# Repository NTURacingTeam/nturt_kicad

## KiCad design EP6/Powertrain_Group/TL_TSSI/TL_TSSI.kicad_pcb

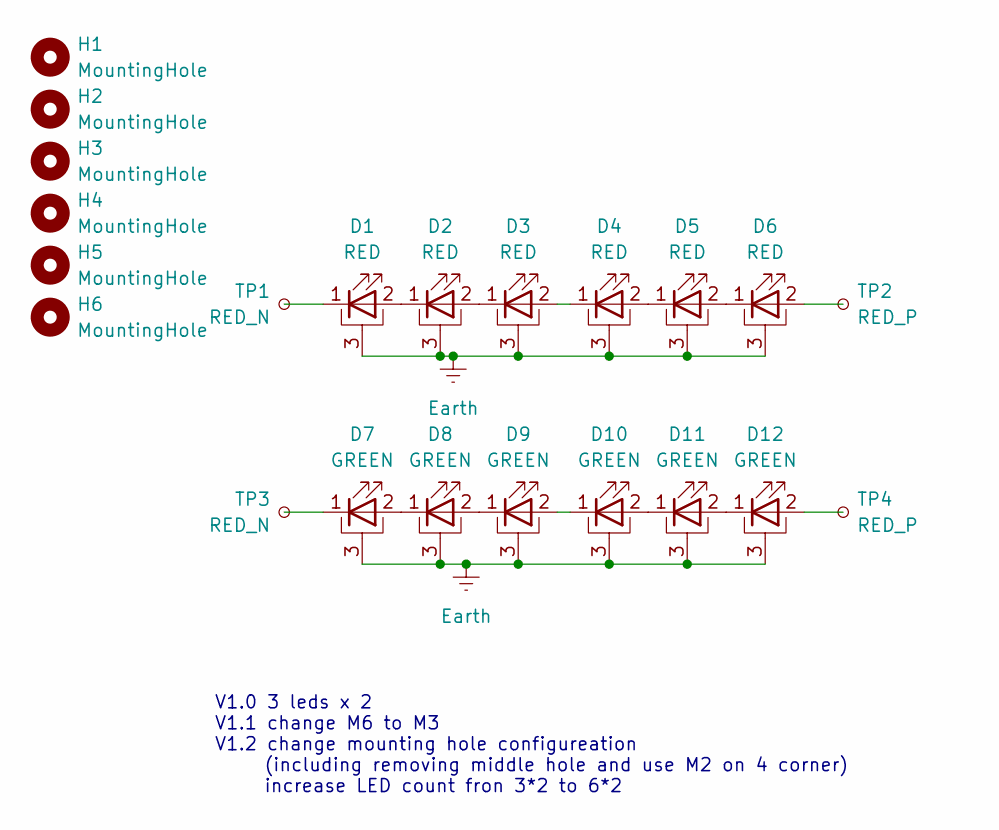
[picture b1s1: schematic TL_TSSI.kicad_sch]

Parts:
D1, D2, D3, D4, D5, D6: RED; LED_1W_3W_R8
D7, D8, D9, D10, D11, D12: GREEN; LED_1W_3W_R8
H1, H2, H3, H4, H5, H6: MountingHole; MountingHole_2.2mm_M2
TP1, TP3: RED_N; TestPoint_Pad_4.0x4.0mm
TP2, TP4: RED_P; TestPoint_Pad_4.0x4.0mm

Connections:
Earth: D1.3 (PAD), D2.3 (PAD), D3.3 (PAD), D4.3 (PAD), D5.3 (PAD), D6.3 (PAD), D7.3 (PAD), D8.3 (PAD), D9.3 (PAD), D10.3 (PAD), D11.3 (PAD), D12.3 (PAD)
unnamed: D1.2 (A), D2.1 (K)
unnamed: D1.1 (K), TP1.1
unnamed: D2.2 (A), D3.1 (K)
unnamed: D3.2 (A), D4.1 (K)
unnamed: D4.2 (A), D5.1 (K)
unnamed: D5.2 (A), D6.1 (K)
unnamed: D6.2 (A), TP2.1
unnamed: D7.2 (A), D8.1 (K)
unnamed: D7.1 (K), TP3.1
unnamed: D8.2 (A), D9.1 (K)
unnamed: D10.2 (A), D11.1 (K)
unnamed: D9.2 (A), D10.1 (K)
unnamed: D11.2 (A), D12.1 (K)
unnamed: D12.2 (A), TP4.1

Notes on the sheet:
V1.0 3 leds x 2 V1.1 change M6 to M3 V1.2 change mounting hole configureation (including removing middle hole and use M2 on 4 corner) increase LED count fron 3*2 to 6*2

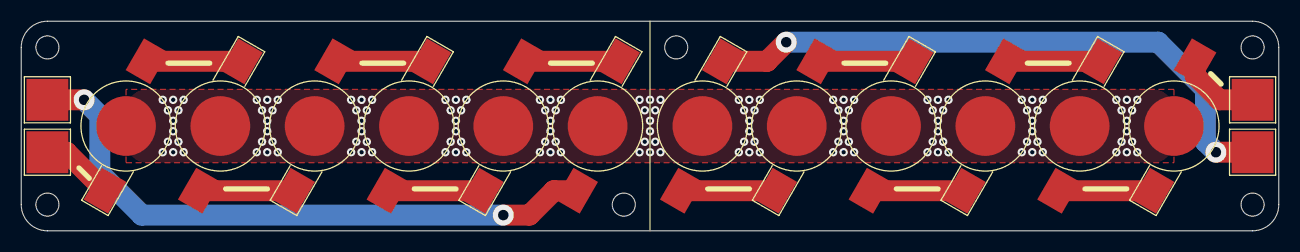
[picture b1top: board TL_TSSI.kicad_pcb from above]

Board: 2 copper layers, 120.0 x 20.0 mm, 22 parts (0 on the bottom side), 15 nets.

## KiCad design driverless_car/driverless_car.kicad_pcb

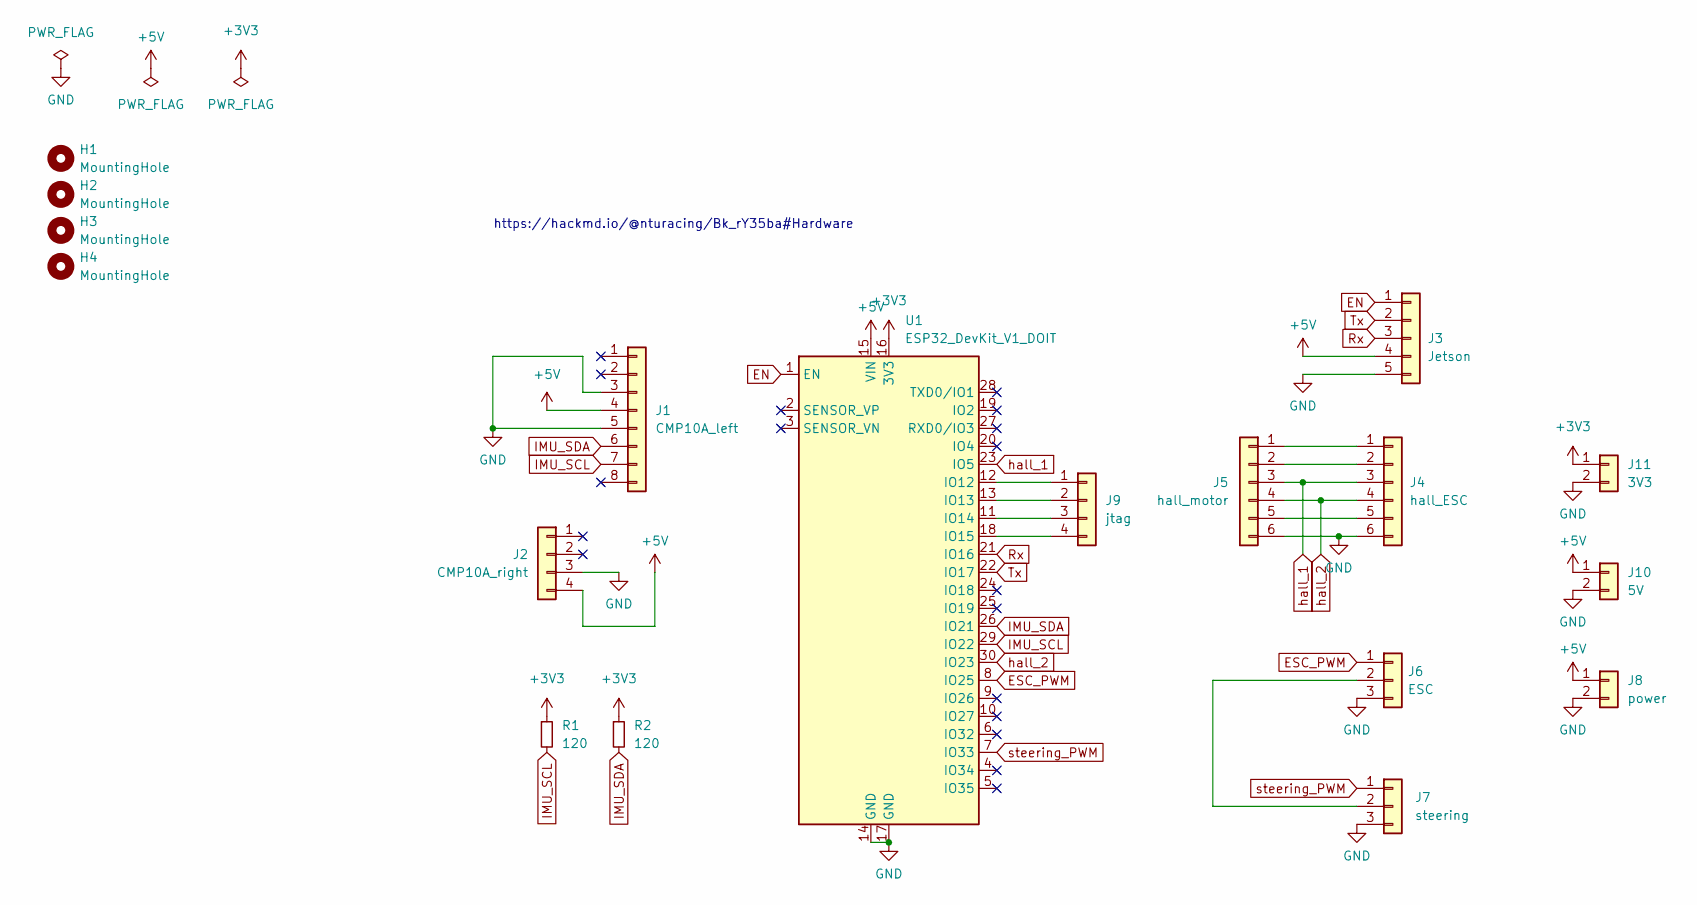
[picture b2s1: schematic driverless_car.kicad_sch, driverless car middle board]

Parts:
H1, H2, H3, H4: MountingHole; MountingHole_3mm
J1: CMP10A_left; PinSocket_1x08_P2.54mm_Vertical
J2: CMP10A_right; PinSocket_1x04_P2.54mm_Vertical
J3: Jetson; JST_XH_B5B-XH-A_1x05_P2.50mm_Vertical
J4: hall_ESC; JST_XH_B6B-XH-A_1x06_P2.50mm_Vertical
J5: hall_motor; JST_XH_B6B-XH-A_1x06_P2.50mm_Vertical
J6: ESC; PinHeader_1x03_P2.54mm_Vertical
J7: steering; PinHeader_1x03_P2.54mm_Vertical
J8: power; PhoenixContact_MSTBVA_2,5_2-G-5,08_1x02_P5.08mm_Vertical
J9: jtag; PinSocket_1x04_P2.54mm_Vertical
J10: 5V; PinSocket_1x02_P2.54mm_Vertical
J11: 3V3; PinSocket_1x02_P2.54mm_Vertical
R1, R2: 120; R_0805_2012Metric
U1: ESP32_DevKit_V1_DOIT; esp32_devkit_v1_doit

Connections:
+3V3: J11.1, R1.1, R2.1, U1.16 (3V3)
+5V: J1.4, J2.4, J3.4, J8.1, J10.1, U1.15 (VIN)
EN: J3.1, U1.1 (EN)
ESC_PWM: J6.1, U1.8 (IO25)
GND: J1.3, J1.5, J2.3, J3.5, J4.6, J5.6, J6.3, J7.3, J8.2, J10.2, J11.2, U1.14 (GND), U1.17 (GND)
IMU_SCL: J1.7, R1.2, U1.29 (IO22)
IMU_SDA: J1.6, R2.2, U1.26 (IO21)
unnamed: J4.1, J5.1
unnamed: J4.2, J5.2
unnamed: J4.5, J5.5
unnamed: J6.2, J7.2
unnamed: J9.1, U1.12 (IO12)
unnamed: J9.2, U1.13 (IO13)
unnamed: J9.3, U1.11 (IO14)
unnamed: J9.4, U1.18 (IO15)
Rx: J3.3, U1.21 (IO16)
Tx: J3.2, U1.22 (IO17)
hall_1: J4.3, J5.3, U1.23 (IO5)
hall_2: J4.4, J5.4, U1.30 (IO23)
steering_PWM: J7.1, U1.7 (IO33)

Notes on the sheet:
https://hackmd.io/@nturacing/Bk_rY35ba#Hardware

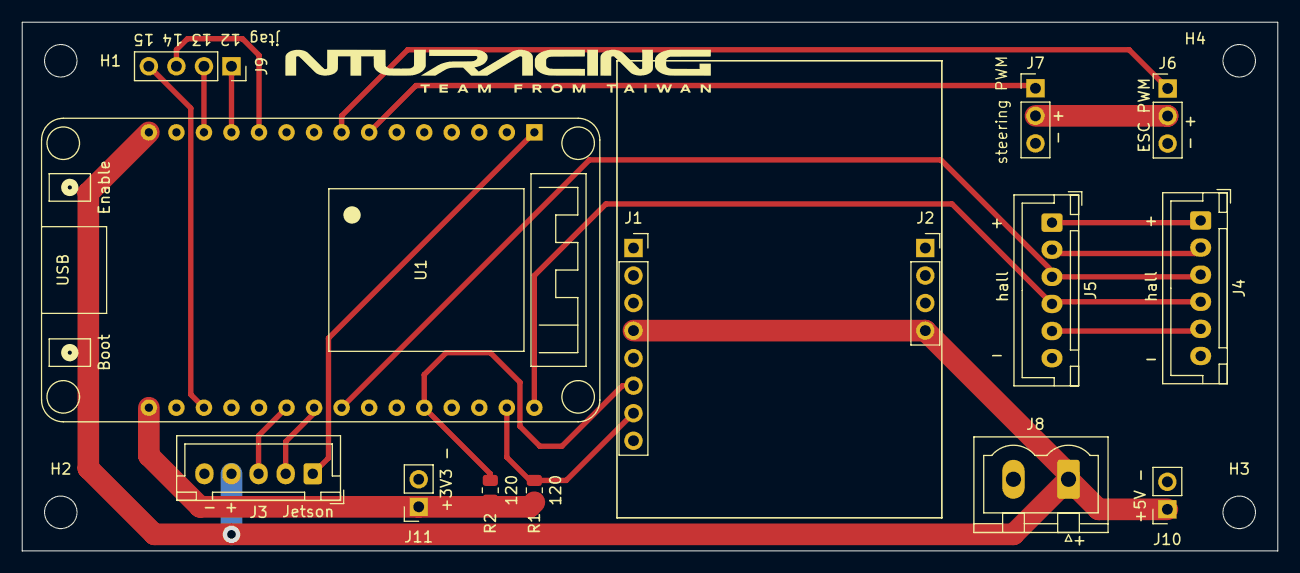
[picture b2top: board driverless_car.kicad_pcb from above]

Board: 2 copper layers, 115.8 x 48.8 mm, 18 parts (0 on the bottom side), 20 nets.
